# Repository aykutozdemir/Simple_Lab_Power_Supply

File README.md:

### Simple Lab Power Supply (4-Channel)

A compact four-channel bench power supply project with dedicated controller, protection, and current-sensing boards, plus a printable enclosure and front panel components. Repository: [`aykutozdemir/Simple_Lab_Power_Supply`](https://github.com/aykutozdemir/Simple_Lab_Power_Supply).

### Features
- **Four independent channels**: adjustable and monitorable per-channel output
- **Dedicated protection**: over-current/short-circuit protection board
- **Current sensing**: separate current sensor design for precise measurement
- **Printable enclosure**: parametric SCAD and exported STLs for all case parts
- **Fabrication-ready**: gerbers, BOMs, PDFs, and 3D previews included

### Repository layout
- `Controller/`: KiCad project for the main control PCB
  - `generated/gerbers/`: fabrication files
  - `generated/bom/`: BOM in CSV/HTML/PDF
  - `generated/pdf/`: PCB and schematic PDFs
  - `generated/3d/`: 3D renders and board STEP/STL
- `Protection/`: KiCad project for the protection PCB
  - `generated/` mirrors the structure above
- `Current_Sensor/`: KiCad project for the current sensor
- `3D/`: mechanical assets and enclosure
  - `exports/`: printable panels and enclosure parts (`front.stl`, `back.stl`, `left.stl`, `right.stl`, `top.stl`, `bottom.stl`, `mid.stl`)
  - subfolders for off-the-shelf or custom components (banana jacks, fan, sockets, switches, knobs, etc.)

### Quick start
1) Open electronics in KiCad (KiCad 7+ recommended):
   - `Controller/Controller.kicad_pro`
   - `Protection/Protection.kicad_pro`
   - `Current_Sensor/Current_Sensor.kicad_pro`
2) Fabrication files:
   - Controller gerbers: `Controller/generated/gerbers/`
   - Protection gerbers: `Protection/generated/gerbers/`
   - BOMs: `Controller/generated/bom/Controller_bom.*`, `Protection/generated/bom/Protection_bom.*`
   - PDFs (schematic/PCB): see `generated/pdf/`
3) Enclosure and front panel:
   - Print from `3D/exports/*.stl`
   - Optional components located in subfolders (e.g., `3D/banana/banana.stl`, `3D/pot/pot.stl`, `3D/fan/fan.stl`)

### 3D printing guidance
- Material: PLA or PETG (PETG recommended for heat resistance)
- Layer height: 0.2 mm (typ.)
- Infill: 15–25% grid/gyroid for panels; 35–50% for brackets
- Walls: 3–4 perimeters; 4–6 top/bottom layers
- Orientation: print panels flat; brackets with load-bearing axis aligned; check STL previews in `3D/exports/`

### Front panel notes
- Displays and meters mount to the `front.stl` panel. Matching cutouts are modeled in the exported panel.
- Banana connectors: use `3D/banana/banana.stl`. In the assembled view, place two banana connectors per multimeter, horizontally below the displays, visible from front. Front panel hole x-offsets at ±12 mm and z at `box_height*4/6 - multimeter_height/2 - 25`. Place connectors at y slightly in front of the front panel (e.g., `box_depth + 1`) and rotate `[-90, 0, 0]` for insertion alignment [[memory:6634135]].

### Electrical overview
- Controller board manages channel outputs, measurement, and user interface.
- Protection board implements fast over-current/short protection and isolation where needed.
- Current sensor board provides per-channel current measurement with appropriate scaling.
- See the comprehensive PDFs in `Controller/generated/pdf/` and `Protection/generated/pdf/` for signal names and interfaces.

### Fabrication and assembly
1) Order PCBs using the gerbers in each project’s `generated/gerbers/` directory.
2) Source parts from the BOMs (`generated/bom/`). Check packages/footprints against PDFs.
3) Solder SMD/TH components as per schematics.
4) Test each board independently before system integration.
5) Assemble enclosure:
   - Dry-fit `front`, `back`, `left`, `right`, `top`, `bottom`, and `mid` panels.
   - Install switches, sockets, fuses, fan, pots/knobs, and banana jacks.
   - Route wiring according to schematics; keep high-current and low-noise paths separated.

### Safety
- Mains voltages and high currents can be hazardous. Verify isolation, fusing, and protective earth where applicable.
- Use appropriate gauge wiring, strain relief, and insulation. Validate thermal performance under load.

### Contributing
- Issues and pull requests are welcome on GitHub: `https://github.com/aykutozdemir/Simple_Lab_Power_Supply`.
- For changes that affect the enclosure, export updated STLs to `3D/exports/` and include screenshots/renders.
- For PCB edits, regenerate `generated/` assets (BOM, PDFs, gerbers) so reviewers can diff artifacts.

### License
No license file is included yet. If you intend to reuse or distribute, please open an issue to clarify licensing, or add a `LICENSE` file.

### Credits
Design and repository maintained by Aykut Ozdemir. See the GitHub repository for history and updates: [`Simple_Lab_Power_Supply`](https://github.com/aykutozdemir/Simple_Lab_Power_Supply).

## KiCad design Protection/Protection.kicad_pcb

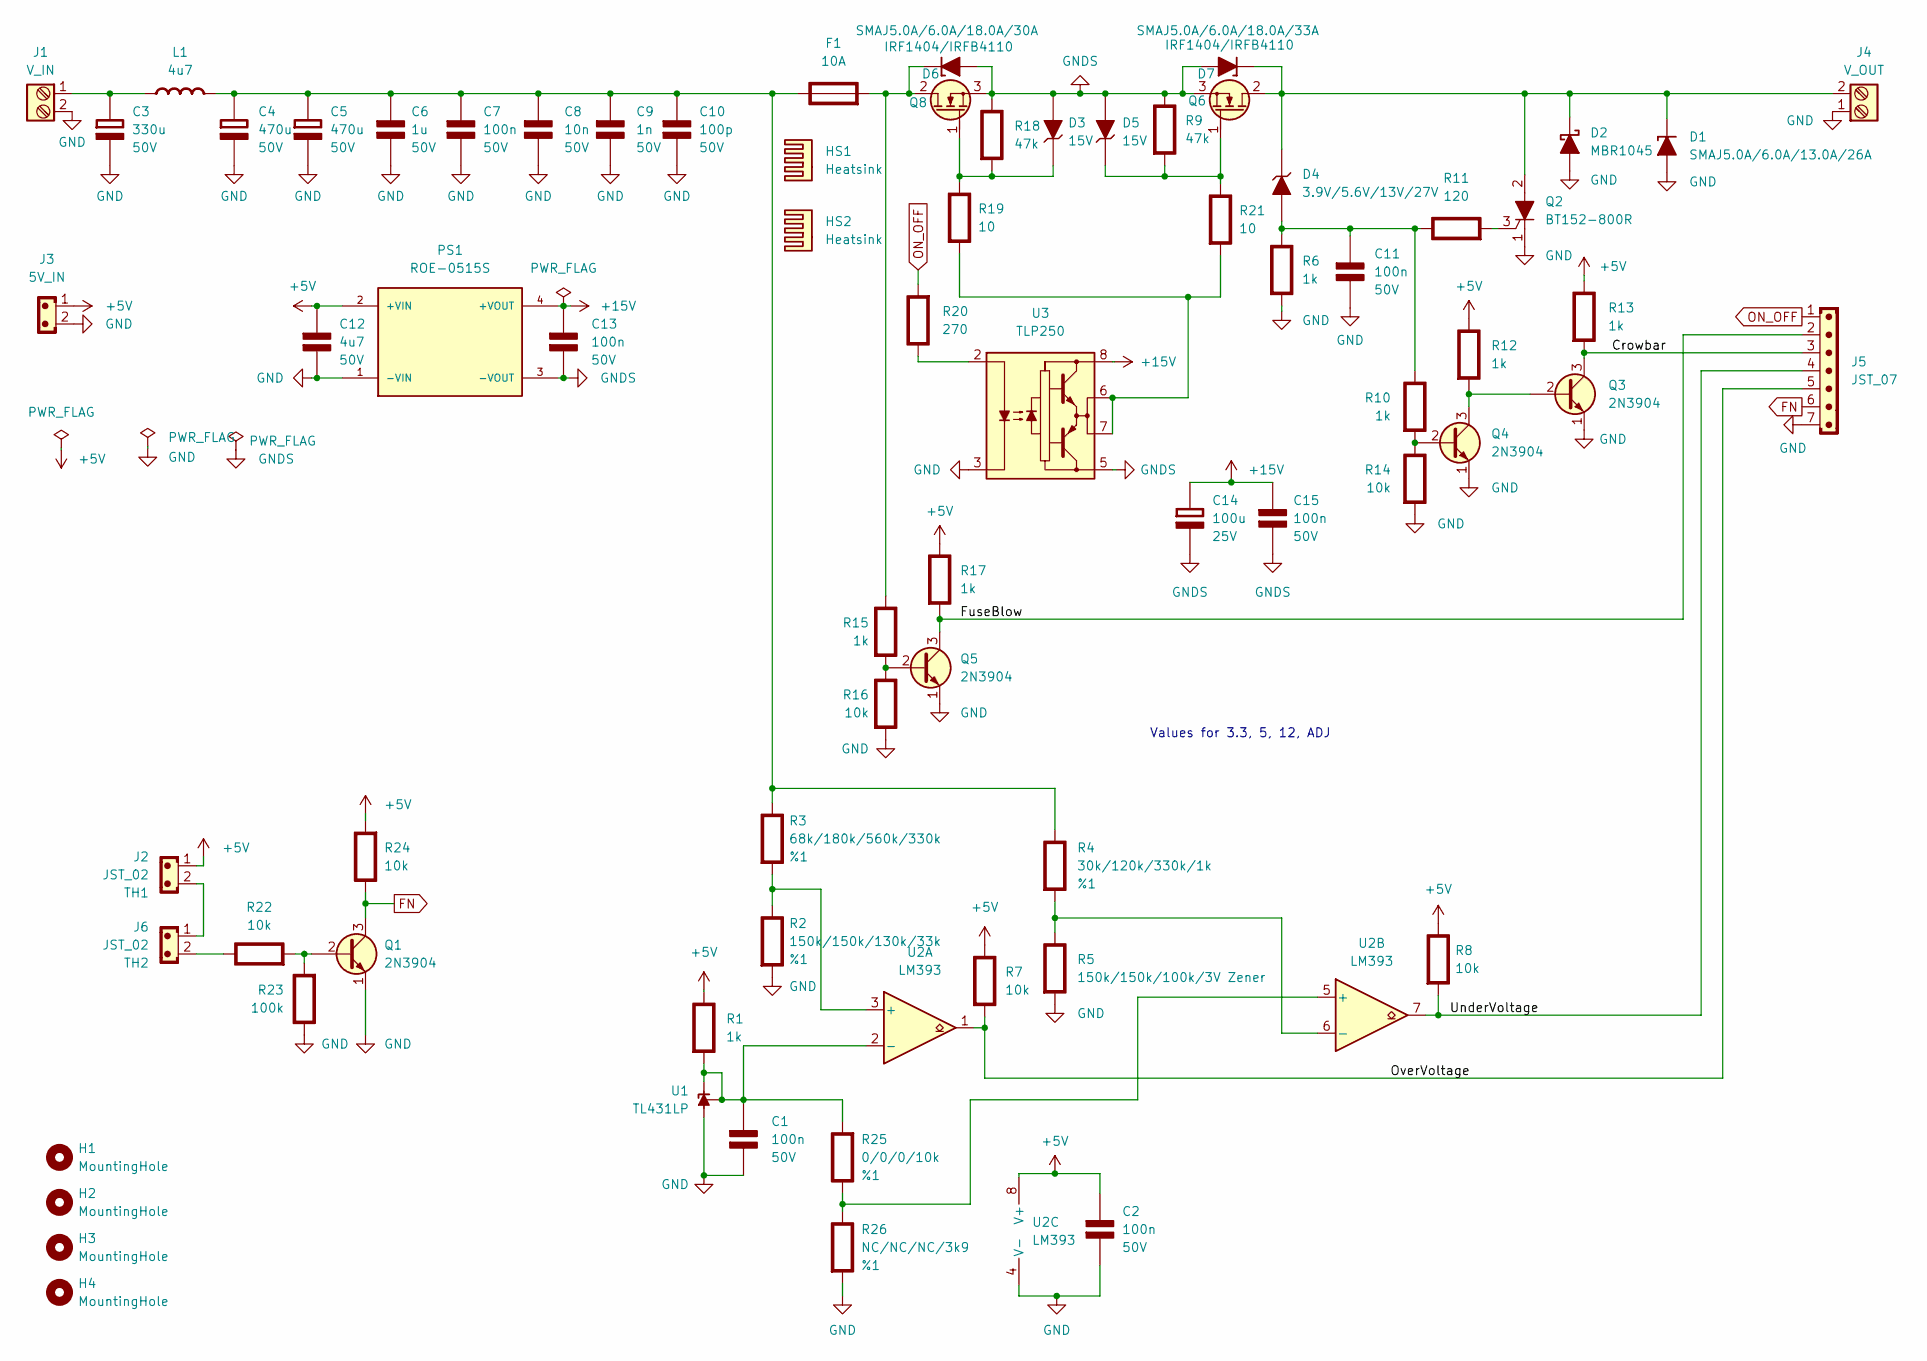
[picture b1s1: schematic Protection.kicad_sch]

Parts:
C1, C2, C7, C11, C13, C15: 100n; C_Disc_D5.0mm_W2.5mm_P5.00mm; Rating 50V
C3: 330u; CP_Radial_D10.0mm_P5.00mm; Rating 50V
C4, C5: 470u; C_Radial_D10.0mm_H20.0mm_P5.00mm; Rating 50V
C6: 1u; C_Disc_D5.0mm_W2.5mm_P5.00mm; Rating 50V
C8: 10n; C_Disc_D5.0mm_W2.5mm_P5.00mm; Rating 50V
C9: 1n; C_Disc_D5.0mm_W2.5mm_P5.00mm; Rating 50V
C10: 100p; C_Disc_D5.0mm_W2.5mm_P5.00mm; Rating 50V
C12: 4u7; C_1206_3216Metric_Pad1.33x1.80mm_HandSolder; Rating 50V
C14: 100u; CP_Radial_D5.0mm_P2.50mm; Rating 25V
D1: SMAJ5.0A/6.0A/13.0A/26A; D_SMA
D2: MBR1045; TO-220-2_Vertical_KA
D3, D5: 15V; D_DO-41_SOD81_P10.16mm_Horizontal
D4: 3.9V/5.6V/13V/27V; D_DO-41_SOD81_P10.16mm_Horizontal
D6: SMAJ5.0A/6.0A/18.0A/30A; D_SMA
D7: SMAJ5.0A/6.0A/18.0A/33A; D_SMA
F1: 10A; TerminalBlock_Phoenix_PT-1,5-2-5.0-H_1x02_P5.00mm_Horizontal
H1, H2, H3, H4: MountingHole; MountingHole_3.2mm_M3_DIN965
HS1, HS2: Heatsink; TO-220_Heatsink
J1: V_IN; TerminalBlock_Phoenix_PT-1,5-2-5.0-H_1x02_P5.00mm_Horizontal
J2, J6: JST_02; JST_EH_B2B-EH-A_1x02_P2.50mm_Vertical
J3: 5V_IN; JST_XH_B2B-XH-A_1x02_P2.50mm_Vertical
J4: V_OUT; TerminalBlock_Phoenix_PT-1,5-2-5.0-H_1x02_P5.00mm_Horizontal
J5: JST_07; JST_XH_B7B-XH-A_1x07_P2.50mm_Vertical
L1: 4u7; L_12x12mm_H8mm; Rating 15A
PS1: ROE-0515S; CONV_ROE-0515S; PARTREV 5
Q1, Q3, Q4, Q5: 2N3904; TO-92_Inline_Wide_EBC
Q2: BT152-800R; TO-220-3_Vertical_KAG
Q6, Q8: IRF1404/IRFB4110; TO-220-3_Vertical_GDS
R1, R6, R10, R12, R13, R15, R17: 1k; R_Axial_DIN0207_L6.3mm_D2.5mm_P10.16mm_Horizontal
R2: 150k/150k/130k/33k; R_Axial_DIN0207_L6.3mm_D2.5mm_P10.16mm_Horizontal; Rating %1
R3: 68k/180k/560k/330k; R_Axial_DIN0207_L6.3mm_D2.5mm_P10.16mm_Horizontal; Rating %1
R4: 30k/120k/330k/1k; R_Axial_DIN0207_L6.3mm_D2.5mm_P10.16mm_Horizontal; Rating %1
R5: 150k/150k/100k/3V Zener; R_Axial_DIN0207_L6.3mm_D2.5mm_P10.16mm_Horizontal; Rating %1
R7, R8: 10k; R_Axial_DIN0207_L6.3mm_D2.5mm_P10.16mm_Horizontal; Rating %1
R9, R18: 47k; R_Axial_DIN0207_L6.3mm_D2.5mm_P10.16mm_Horizontal
R11: 120; R_Axial_DIN0207_L6.3mm_D2.5mm_P10.16mm_Horizontal
R14, R16, R22, R24: 10k; R_Axial_DIN0207_L6.3mm_D2.5mm_P10.16mm_Horizontal
R19, R21: 10; R_Axial_DIN0207_L6.3mm_D2.5mm_P10.16mm_Horizontal
R20: 270; R_Axial_DIN0207_L6.3mm_D2.5mm_P10.16mm_Horizontal
R23: 100k; R_Axial_DIN0207_L6.3mm_D2.5mm_P10.16mm_Horizontal
R25: 0/0/0/10k; R_Axial_DIN0207_L6.3mm_D2.5mm_P10.16mm_Horizontal; Rating %1
R26: NC/NC/NC/3k9; R_Axial_DIN0207_L6.3mm_D2.5mm_P10.16mm_Horizontal; Rating %1
U1: TL431LP; TO-92_Inline
U2: LM393; DIP-8_W7.62mm_Socket
U3: TLP250; DIP-8_W7.62mm

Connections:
+5V: C2.1 (+), C12.1 (+), J2.1, J3.1, PS1.2 (+VIN), R1.1 (+), R7.1 (+), R8.1 (+), R12.1 (+), R13.1 (+), R17.1 (+), R24.2 (-), U2.8 (V+)
+15V: C13.1 (+), C14.1 (+), C15.1 (+), PS1.4 (+VOUT), U3.8 (VCC)
/Crowbar: J5.3, Q3.3 (C), R13.2 (-)
/FuseBlow: J5.2, Q5.3 (C), R17.2 (-)
/OverVoltage: J5.5, R7.2 (-), U2.1
/UnderVoltage: J5.4, R8.2 (-), U2.7
FN: J5.6, Q1.3 (C), R24.1 (+)
GND: C1.2 (-), C2.2 (-), C3.2 (-), C4.2 (-), C5.2 (-), C6.2 (-), C7.2 (-), C8.2 (-), C9.2 (-), C10.2 (-), C11.2 (-), C12.2 (-), D1.2 (A), D2.2 (A), J1.2, J3.2, J4.1, J5.7, PS1.1 (-VIN), Q1.1 (E), Q2.1 (K), Q3.1 (E), Q4.1 (E), Q5.1 (E), R2.2 (-), R5.2 (-), R6.2 (-), R14.2 (-), R16.2 (-), R23.1 (+), R26.2 (-), U1.2 (A), U2.4 (V-), U3.3 (C)
GNDS: C13.2 (-), C14.2 (-), C15.2 (-), D3.1 (A), D5.1 (A), D6.2 (A), D7.2 (A), PS1.3 (-VOUT), Q6.3 (S), Q8.3 (S), R9.1 (+), R18.1 (+), U3.5 (VEE)
unnamed: C1.1 (+), R1.2 (-), R25.2 (-), U1.1 (REF), U1.3 (K), U2.2 (-)
unnamed: C3.1 (+), J1.1, L1.1 (+)
unnamed: C4.1 (+), C5.1 (+), C6.1 (+), C7.1 (+), C8.1 (+), C9.1 (+), C10.1 (+), F1.1 (+), L1.2 (-), R3.1 (+), R4.1 (+)
unnamed: C11.1 (+), D4.1 (A), R6.1 (+), R10.1 (+), R11.1 (+)
unnamed: D1.1 (K), D2.1 (K), D4.2 (K), D7.1 (K), J4.2, Q2.2 (A), Q6.2 (D)
unnamed: D3.2 (K), Q8.1 (G), R18.2 (-), R19.1 (+)
unnamed: D5.2 (K), Q6.1 (G), R9.2 (-), R21.1 (+)
unnamed: D6.1 (K), F1.2 (-), Q8.2 (D), R15.1 (+)
unnamed: J2.2, J6.1
unnamed: Q1.2 (B), R22.2 (-), R23.2 (-)
unnamed: Q2.3 (G), R11.2 (-)
unnamed: Q3.2 (B), Q4.3 (C), R12.2 (-)
unnamed: Q4.2 (B), R10.2 (-), R14.1 (+)
unnamed: Q5.2 (B), R15.2 (-), R16.1 (+)
unnamed: R2.1 (+), R3.2 (-), U2.3 (+)
unnamed: R4.2 (-), R5.1 (+), U2.6 (-)
unnamed: R19.2 (-), R21.2 (-), U3.6 (VO), U3.7 (VO)
unnamed: R20.1 (+), U3.2 (A)
unnamed: J6.2, R22.1 (+)
unnamed: R25.1 (+), R26.1 (+), U2.5 (+)
ON_OFF: J5.1, R20.2 (-)

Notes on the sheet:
Values for 3.3, 5, 12, ADJ

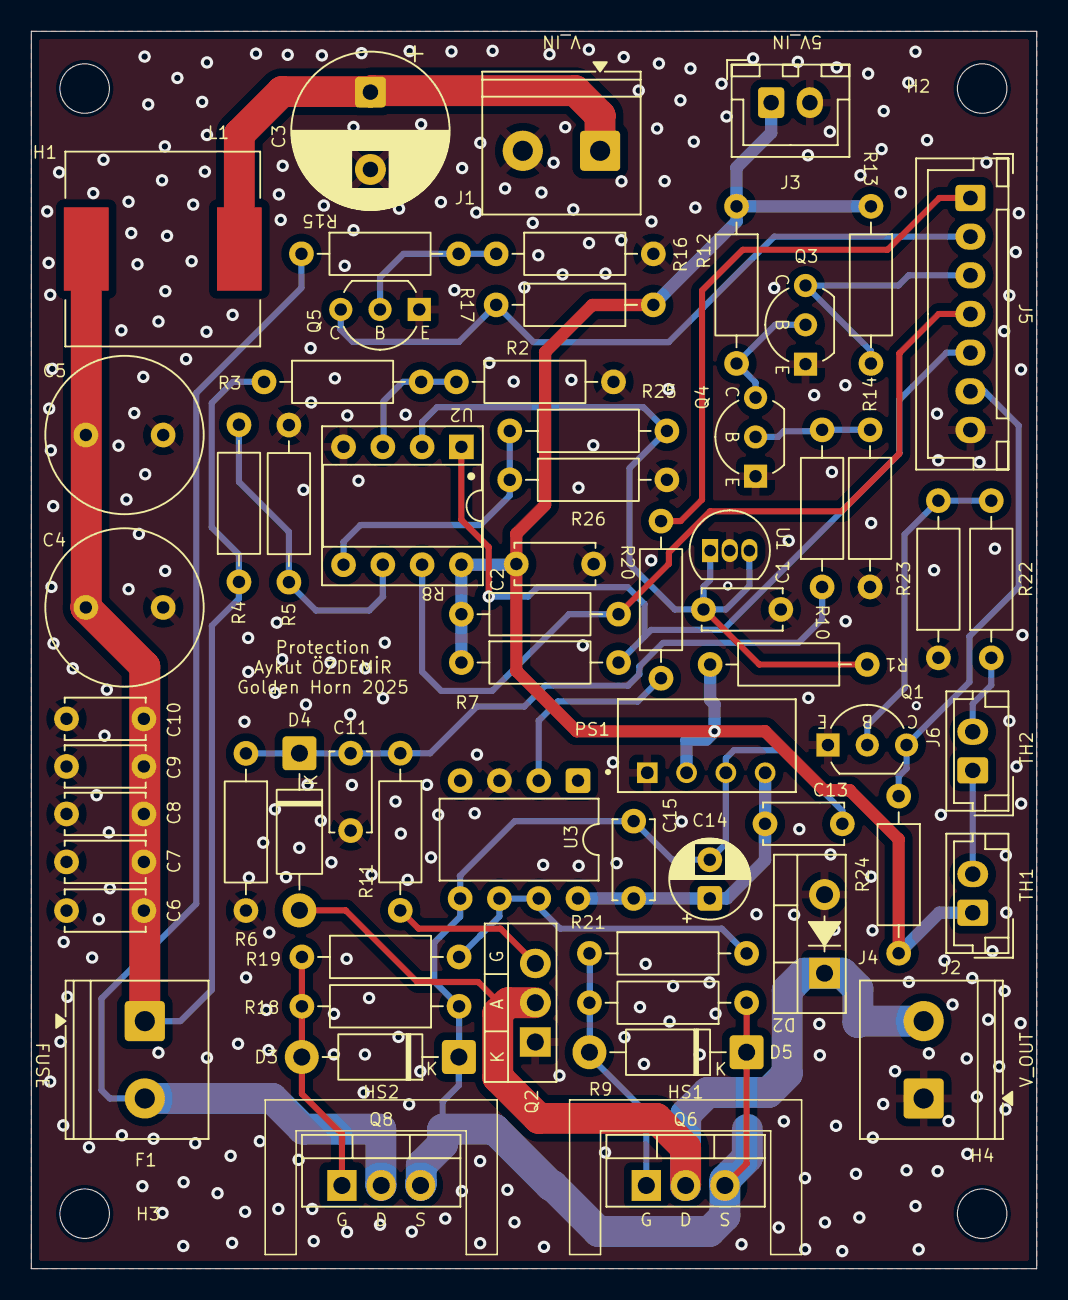
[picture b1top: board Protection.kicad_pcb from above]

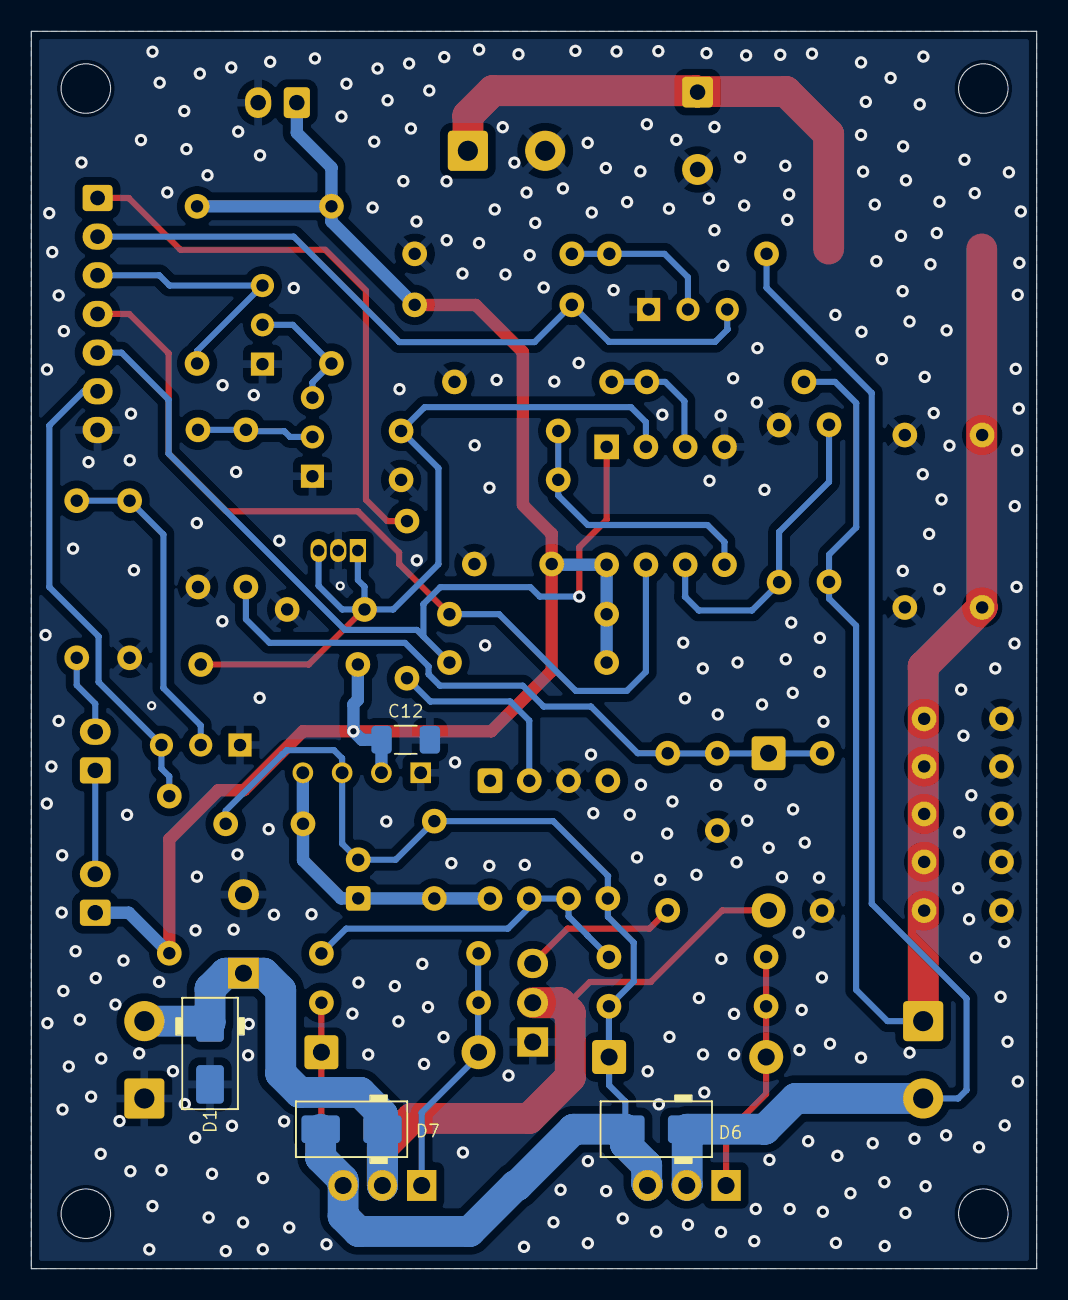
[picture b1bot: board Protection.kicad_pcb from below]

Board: 2 copper layers, 65.0 x 80.0 mm, 73 parts (4 on the bottom side), 30 nets.

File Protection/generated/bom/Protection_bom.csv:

"Refs","Value","Footprint","Qty","Rating"
"C10","100p","Capacitor_THT:C_Disc_D5.0mm_W2.5mm_P5.00mm","1","50V"
"C9","1n","Capacitor_THT:C_Disc_D5.0mm_W2.5mm_P5.00mm","1","50V"
"C8","10n","Capacitor_THT:C_Disc_D5.0mm_W2.5mm_P5.00mm","1","50V"
"C1,C2,C7,C11,C13,C15","100n","Capacitor_THT:C_Disc_D5.0mm_W2.5mm_P5.00mm","6","50V"
"C6","1u","Capacitor_THT:C_Disc_D5.0mm_W2.5mm_P5.00mm","1","50V"
"C14","100u","Capacitor_THT:CP_Radial_D5.0mm_P2.50mm","1","25V"
"C3","330u","Capacitor_THT:CP_Radial_D10.0mm_P5.00mm","1","50V"
"C4,C5","470u","Capacitor_THT:C_Radial_D10.0mm_H20.0mm_P5.00mm","2","50V"
"J3","5V_IN","Connector_JST:JST_XH_B2B-XH-A_1x02_P2.50mm_Vertical","1",""
"F1","10A","TerminalBlock_Phoenix:TerminalBlock_Phoenix_PT-1,5-2-5.0-H_1x02_P5.00mm_Horizontal","1",""
"R19,R21","10","Resistor_THT:R_Axial_DIN0207_L6.3mm_D2.5mm_P10.16mm_Horizontal","2",""
"D3,D5","15V","Diode_THT:D_DO-41_SOD81_P10.16mm_Horizontal","2",""
"R11","120","Resistor_THT:R_Axial_DIN0207_L6.3mm_D2.5mm_P10.16mm_Horizontal","1",""
"R20","270","Resistor_THT:R_Axial_DIN0207_L6.3mm_D2.5mm_P10.16mm_Horizontal","1",""
"R1,R6,R10,R12,R13,R15,R17","1k","Resistor_THT:R_Axial_DIN0207_L6.3mm_D2.5mm_P10.16mm_Horizontal","7",""
"R7,R8","10k","Resistor_THT:R_Axial_DIN0207_L6.3mm_D2.5mm_P10.16mm_Horizontal","2","%1"
"R14,R16,R22,R24","10k","Resistor_THT:R_Axial_DIN0207_L6.3mm_D2.5mm_P10.16mm_Horizontal","4",""
"R9,R18","47k","Resistor_THT:R_Axial_DIN0207_L6.3mm_D2.5mm_P10.16mm_Horizontal","2",""
"R23","100k","Resistor_THT:R_Axial_DIN0207_L6.3mm_D2.5mm_P10.16mm_Horizontal","1",""
"R25","0/0/0/10k","Resistor_THT:R_Axial_DIN0207_L6.3mm_D2.5mm_P10.16mm_Horizontal","1","%1"
"R5","150k/150k/100k/3V Zener","Resistor_THT:R_Axial_DIN0207_L6.3mm_D2.5mm_P10.16mm_Horizontal","1","%1"
"R2","150k/150k/130k/33k","Resistor_THT:R_Axial_DIN0207_L6.3mm_D2.5mm_P10.16mm_Horizontal","1","%1"
"Q1,Q3-Q5","2N3904","PCM_Package_TO_SOT_THT_AKL:TO-92_Inline_Wide_EBC","4",""
"D4","3.9V/5.6V/13V/27V","Diode_THT:D_DO-41_SOD81_P10.16mm_Horizontal","1",""
"R4","30k/120k/330k/1k","Resistor_THT:R_Axial_DIN0207_L6.3mm_D2.5mm_P10.16mm_Horizontal","1","%1"
"C12","4u7","Capacitor_SMD:C_1206_3216Metric_Pad1.33x1.80mm_HandSolder","1","50V"
"L1","4u7","Inductor_SMD:L_12x12mm_H8mm","1","15A"
"R3","68k/180k/560k/330k","Resistor_THT:R_Axial_DIN0207_L6.3mm_D2.5mm_P10.16mm_Horizontal","1","%1"
"Q2","BT152-800R","PCM_Package_TO_SOT_THT_AKL:TO-220-3_Vertical_KAG","1",""
"HS1,HS2","Heatsink","Power_Module_Library:TO-220_Heatsink","2",""
"Q6,Q8","IRF1404/IRFB4110","PCM_Package_TO_SOT_THT_AKL:TO-220-3_Vertical_GDS","2",""
"J2,J6","JST_02","Connector_JST:JST_EH_B2B-EH-A_1x02_P2.50mm_Vertical","2",""
"J5","JST_07","Connector_JST:JST_XH_B7B-XH-A_1x07_P2.50mm_Vertical","1",""
"U2","LM393","PCM_Package_DIP_AKL:DIP-8_W7.62mm_Socket","1",""
"D2","MBR1045","PCM_Package_TO_SOT_THT_AKL:TO-220-2_Vertical_KA","1",""
"R26","NC/NC/NC/3k9","Resistor_THT:R_Axial_DIN0207_L6.3mm_D2.5mm_P10.16mm_Horizontal","1","%1"
"PS1","ROE-0515S","Isolation_Trafo:CONV_ROE-0515S","1",""
"D1","SMAJ5.0A/6.0A/13.0A/26A","PCM_Diode_SMD_AKL:D_SMA","1",""
"D6","SMAJ5.0A/6.0A/18.0A/30A","PCM_Diode_SMD_AKL:D_SMA","1",""
"D7","SMAJ5.0A/6.0A/18.0A/33A","PCM_Diode_SMD_AKL:D_SMA","1",""
"U1","TL431LP","Package_TO_SOT_THT:TO-92_Inline","1",""
"U3","TLP250","Package_DIP:DIP-8_W7.62mm","1",""
"J1","V_IN","TerminalBlock_Phoenix:TerminalBlock_Phoenix_PT-1,5-2-5.0-H_1x02_P5.00mm_Horizontal","1",""
"J4","V_OUT","TerminalBlock_Phoenix:TerminalBlock_Phoenix_PT-1,5-2-5.0-H_1x02_P5.00mm_Horizontal","1",""

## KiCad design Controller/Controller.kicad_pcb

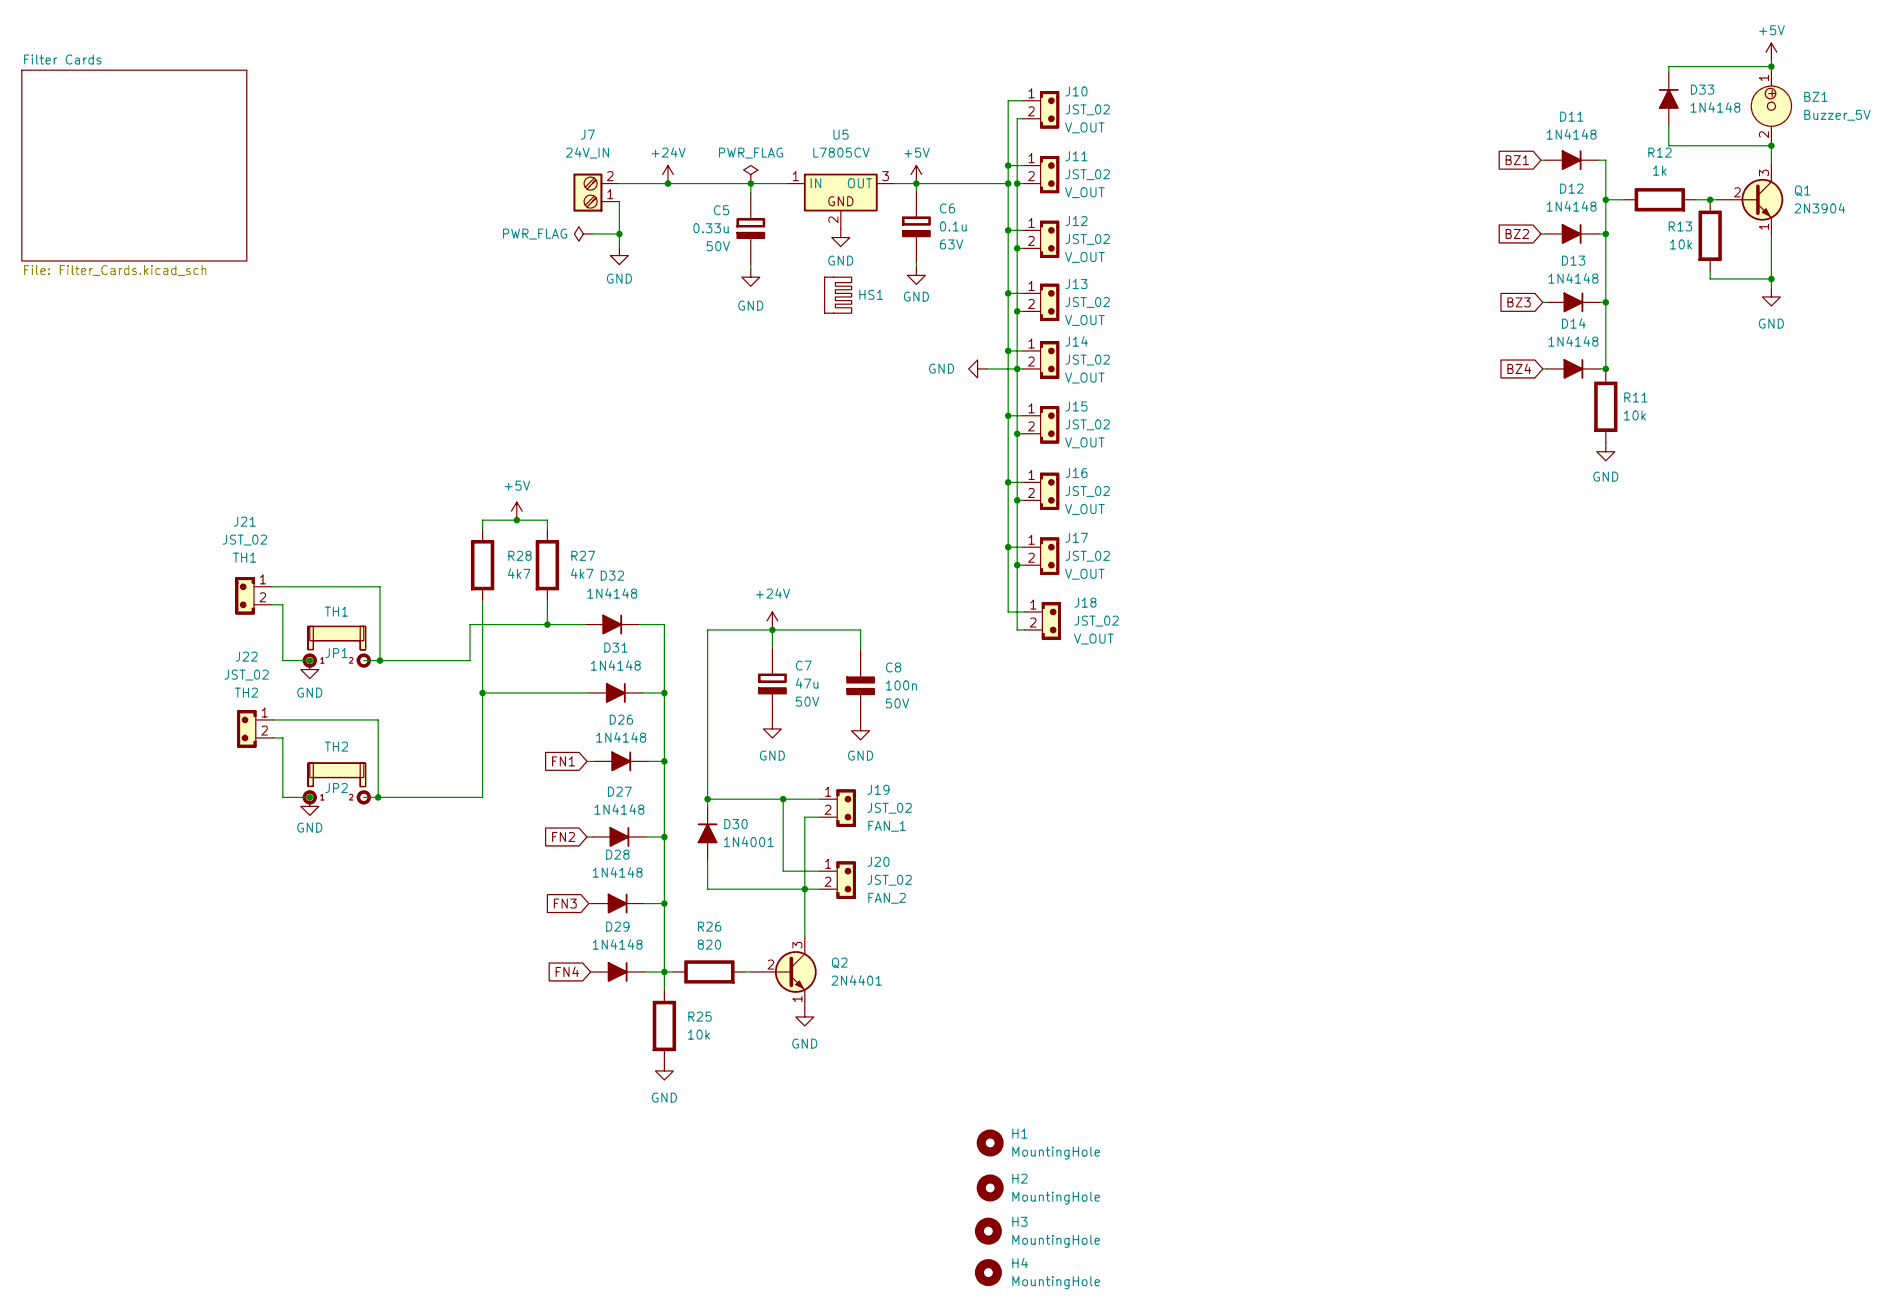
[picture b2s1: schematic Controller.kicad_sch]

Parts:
BZ1: Buzzer_5V; Buzzer_12x9.5RM7.6
C5: 0.33u; CP_Radial_Tantal_D5.5mm_P5.00mm; Rating 50V
C6: 0.1u; CP_Radial_Tantal_D5.5mm_P5.00mm; Rating 63V
C7: 47u; C_Radial_D6.3mm_H11.0mm_P2.50mm; Rating 50V
C8: 100n; C_Disc_D5.0mm_W2.5mm_P5.00mm; Rating 50V
D11, D12, D13, D14, D26, D27, D28, D29, D31, D32, D33: 1N4148; D_DO-35_SOD27_P7.62mm_Horizontal
D30: 1N4001; D_DO-41_SOD81_P7.62mm_Horizontal
H1, H2, H3, H4: MountingHole; MountingHole_3.2mm_M3_DIN965
HS1: Heatsink_Generic; TO-220_Heatsink
J7: Screw_Terminal_2_P5.00mm; TerminalBlock_Phoenix_PT-1,5-2-5.0-H_1x02_P5.00mm_Horizontal
J10, J11, J12, J13, J14, J15, J16, J17, J18, J19, J20, J21, J22: JST_02; JST_XH_B2B-XH-A_1x02_P2.50mm_Vertical
JP1, JP2: PinHeader_1x02_P2.54mm_Vertical
Q1: 2N3904; TO-92_Inline_Wide_EBC
Q2: 2N4401; TO-92_Inline_Wide_EBC
R11, R13, R25: 10k; R_Axial_DIN0207_L6.3mm_D2.5mm_P10.16mm_Horizontal
R12: 1k; R_Axial_DIN0207_L6.3mm_D2.5mm_P10.16mm_Horizontal
R26: 820; R_Axial_DIN0207_L6.3mm_D2.5mm_P10.16mm_Horizontal
R27, R28: 4k7; R_Axial_DIN0207_L6.3mm_D2.5mm_P10.16mm_Horizontal
U5: L7805CV; TO-220-3_Vertical

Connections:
+5V: BZ1.1, C6.1 (+), D33.1 (K), J10.1, J11.1, J12.1, J13.1, J14.1, J15.1, J16.1, J17.1, J18.1, R27.1 (+), R28.1 (+), U5.3 (OUT); also elsewhere on the board
+24V: C5.1 (+), C7.1 (+), C8.1 (+), D30.1 (K), J7.2, J19.1, J20.1, U5.1 (IN)
BZ1: D11.2 (A); also elsewhere on the board
BZ2: D12.2 (A); also elsewhere on the board
BZ3: D13.2 (A); also elsewhere on the board
BZ4: D14.2 (A); also elsewhere on the board
FN1: D26.2 (A); also elsewhere on the board
FN2: D27.2 (A); also elsewhere on the board
FN3: D28.2 (A); also elsewhere on the board
FN4: D29.2 (A); also elsewhere on the board
GND: C5.2 (-), C6.2 (-), C7.2 (-), C8.2 (-), J7.1, J10.2, J11.2, J12.2, J13.2, J14.2, J15.2, J16.2, J17.2, J18.2, J21.2, J22.2, JP1.1, JP2.1, Q1.1 (E), Q2.1 (E), R11.2 (-), R13.2 (-), R25.2 (-), U5.2; also elsewhere on the board
unnamed: D11.1 (K), D12.1 (K), D13.1 (K), D14.1 (K), R11.1 (+), R12.1 (+)
unnamed: D26.1 (K), D27.1 (K), D28.1 (K), D29.1 (K), D31.1 (K), D32.1 (K), R25.1 (+), R26.1 (+)
unnamed: D30.2 (A), J19.2, J20.2, Q2.3 (C)
unnamed: D31.2 (A), J22.1, JP2.2, R28.2 (-)
unnamed: D32.2 (A), J21.1, JP1.2, R27.2 (-)
unnamed: BZ1.2, D33.2 (A), Q1.3 (C)
unnamed: Q1.2 (B), R12.2 (-), R13.1 (+)
unnamed: Q2.2 (B), R26.2 (-)

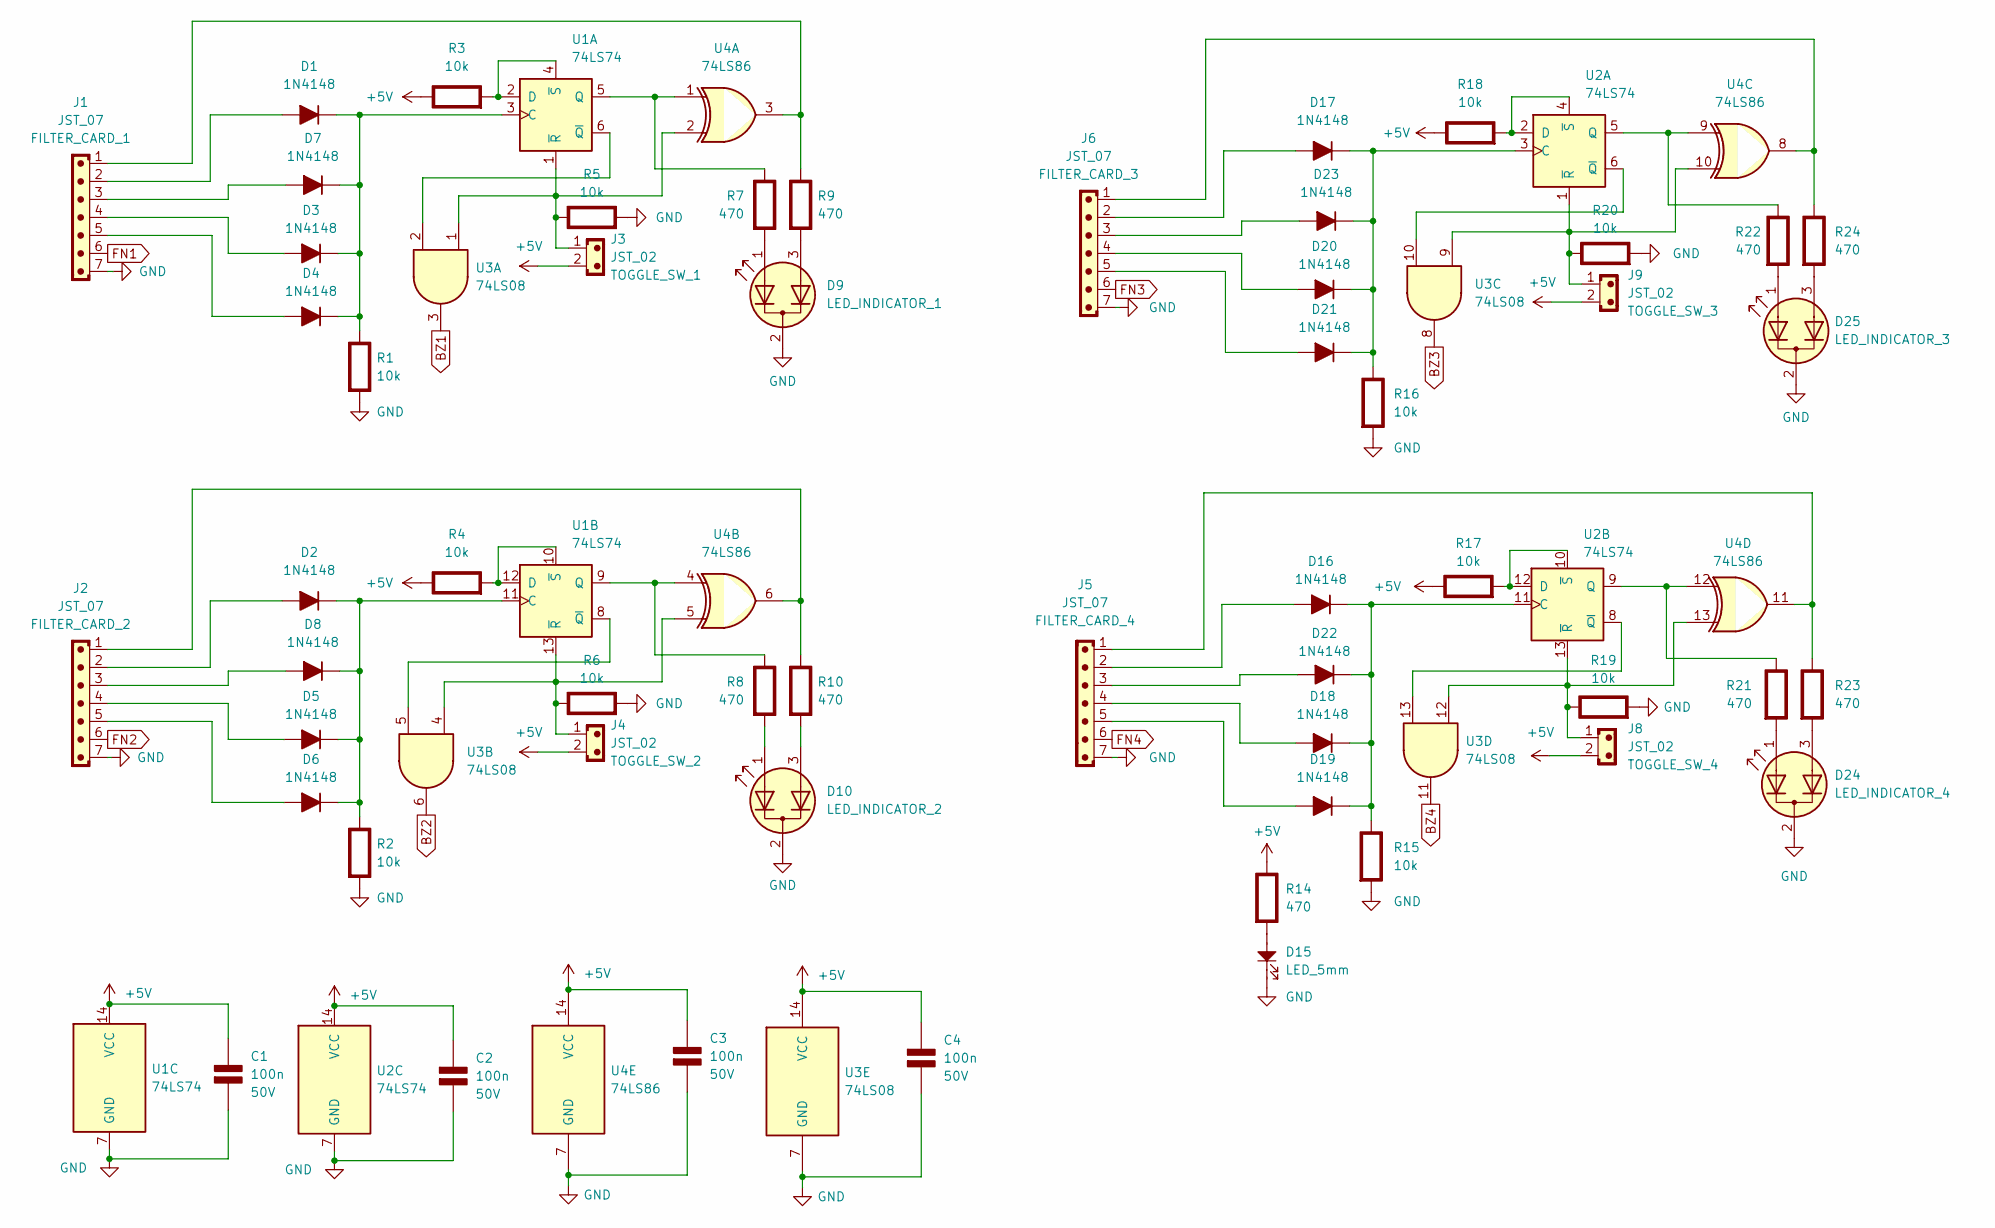
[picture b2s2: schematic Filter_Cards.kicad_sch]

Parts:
C1, C2, C3, C4: 100n; C_Disc_D5.0mm_W2.5mm_P5.00mm; Rating 50V
D1, D2, D3, D4, D5, D6, D7, D8, D16, D17, D18, D19, D20, D21, D22, D23: 1N4148; D_DO-35_SOD27_P7.62mm_Horizontal
D9, D10, D24, D25: LED_Dual_AKA; JST_XH_B3B-XH-A_1x03_P2.50mm_Vertical
D15: LED_5mm; JST_XH_B2B-XH-A_1x02_P2.50mm_Vertical
J1, J2, J5, J6: JST_07; JST_XH_B7B-XH-A_1x07_P2.50mm_Vertical
J3, J4, J8, J9: JST_02; JST_XH_B2B-XH-A_1x02_P2.50mm_Vertical
R1, R2, R15, R16: 10k; R_Axial_DIN0207_L6.3mm_D2.5mm_P10.16mm_Horizontal
R3, R4, R5, R6, R17, R18, R19, R20: 10k; R_Axial_DIN0207_L6.3mm_D2.5mm_P10.16mm_Horizontal; Rating %1
R7, R8, R9, R10, R14, R21, R22, R23, R24: 470; R_Axial_DIN0207_L6.3mm_D2.5mm_P10.16mm_Horizontal; Rating %1
U1, U2: 74LS74; DIP-14_W7.62mm_Socket
U3: 74LS08; DIP-14_W7.62mm_Socket
U4: 74LS86; DIP-14_W7.62mm_Socket

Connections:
+5V: C1.1 (+), C2.1 (+), C3.1 (+), C4.1 (+), J3.2, J4.2, J8.2, J9.2, R3.1 (+), R4.1 (+), R14.1 (+), R17.1 (+), R18.1 (+), U1.14 (VCC), U2.14 (VCC), U3.14 (VCC), U4.14 (VCC); also elsewhere on the board
BZ1: U3.3; also elsewhere on the board
BZ2: U3.6; also elsewhere on the board
BZ3: U3.8; also elsewhere on the board
BZ4: U3.11; also elsewhere on the board
FN1: J1.6; also elsewhere on the board
FN2: J2.6; also elsewhere on the board
FN3: J6.6; also elsewhere on the board
FN4: J5.6; also elsewhere on the board
GND: C1.2 (-), C2.2 (-), C3.2 (-), C4.2 (-), D9.2 (K), D10.2 (K), D15.1, D24.2 (K), D25.2 (K), J1.7, J2.7, J5.7, J6.7, R1.2 (-), R2.2 (-), R5.2 (-), R6.2 (-), R15.2 (-), R16.2 (-), R19.2 (-), R20.2 (-), U1.7 (GND), U2.7 (GND), U3.7 (GND), U4.7 (GND); also elsewhere on the board
unnamed: D1.2 (A), J1.2
unnamed: D1.1 (K), D3.1 (K), D4.1 (K), D7.1 (K), R1.1 (+), U1.3 (C)
unnamed: D2.2 (A), J2.2
unnamed: D2.1 (K), D5.1 (K), D6.1 (K), D8.1 (K), R2.1 (+), U1.11 (C)
unnamed: D3.2 (A), J1.4
unnamed: D4.2 (A), J1.5
unnamed: D5.2 (A), J2.4
unnamed: D6.2 (A), J2.5
unnamed: D7.2 (A), J1.3
unnamed: D8.2 (A), J2.3
unnamed: D9.1 (A1), R7.2 (-)
unnamed: D9.3 (A2), R9.2 (-)
unnamed: D10.1 (A1), R8.2 (-)
unnamed: D10.3 (A2), R10.2 (-)
unnamed: D16.2 (A), J5.2
unnamed: D16.1 (K), D18.1 (K), D19.1 (K), D22.1 (K), R15.1 (+), U2.11 (C)
unnamed: D17.2 (A), J6.2
unnamed: D17.1 (K), D20.1 (K), D21.1 (K), D23.1 (K), R16.1 (+), U2.3 (C)
unnamed: D18.2 (A), J5.4
unnamed: D19.2 (A), J5.5
unnamed: D20.2 (A), J6.4
unnamed: D21.2 (A), J6.5
unnamed: D22.2 (A), J5.3
unnamed: D23.2 (A), J6.3
unnamed: D24.1 (A1), R21.2 (-)
unnamed: D24.3 (A2), R23.2 (-)
unnamed: D25.1 (A1), R22.2 (-)
unnamed: D25.3 (A2), R24.2 (-)
unnamed: R3.2 (-), U1.2 (D), U1.4 (~S)
unnamed: R4.2 (-), U1.10 (~S), U1.12 (D)
unnamed: J3.1, R5.1 (+), U1.1 (~R), U3.1, U4.2
unnamed: J4.1, R6.1 (+), U1.13 (~R), U3.4, U4.5
unnamed: R7.1 (+), U1.5 (Q), U4.1
unnamed: R8.1 (+), U1.9 (Q), U4.4
unnamed: J1.1, R9.1 (+), U4.3
unnamed: J2.1, R10.1 (+), U4.6
unnamed: D15.2, R14.2 (-)
unnamed: R17.2 (-), U2.10 (~S), U2.12 (D)
unnamed: R18.2 (-), U2.2 (D), U2.4 (~S)
unnamed: J8.1, R19.1 (+), U2.13 (~R), U3.12, U4.13
unnamed: J9.1, R20.1 (+), U2.1 (~R), U3.9, U4.10
unnamed: R21.1 (+), U2.9 (Q), U4.12
unnamed: R22.1 (+), U2.5 (Q), U4.9
unnamed: J5.1, R23.1 (+), U4.11
unnamed: J6.1, R24.1 (+), U4.8
unnamed: U1.6 (~Q), U3.2
unnamed: U1.8 (~Q), U3.5
unnamed: U2.6 (~Q), U3.10
unnamed: U2.8 (~Q), U3.13

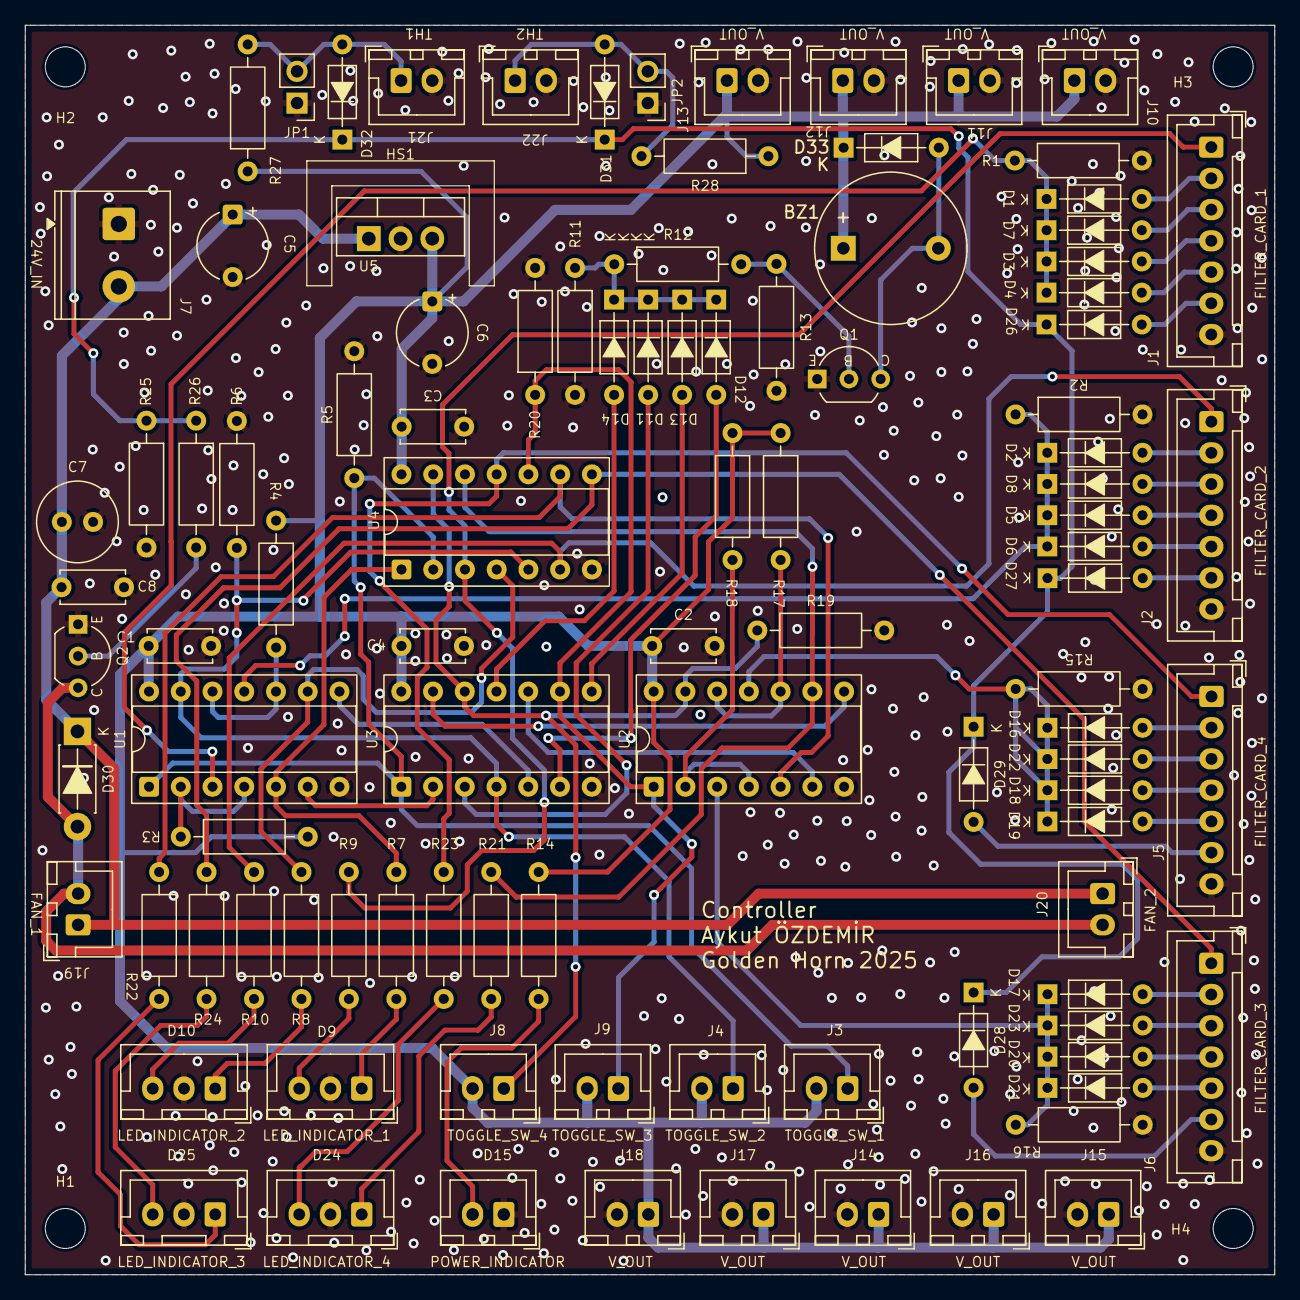
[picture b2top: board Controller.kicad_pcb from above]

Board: 2 copper layers, 100.0 x 100.0 mm, 106 parts (0 on the bottom side), 68 nets.

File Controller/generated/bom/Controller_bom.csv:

"Refs","Value","Footprint","Qty","Rating"
"C6","0.1u","Capacitor_THT:CP_Radial_Tantal_D5.5mm_P5.00mm","1","63V"
"C1-C4,C8","100n","Capacitor_THT:C_Disc_D5.0mm_W2.5mm_P5.00mm","5","50V"
"C5","0.33u","Capacitor_THT:CP_Radial_Tantal_D5.5mm_P5.00mm","1","50V"
"C7","47u","Capacitor_THT:C_Radial_D6.3mm_H11.0mm_P2.50mm","1","50V"
"R7-R10,R14,R21-R24","470","Resistor_THT:R_Axial_DIN0207_L6.3mm_D2.5mm_P10.16mm_Horizontal","9","%1"
"R26","820","Resistor_THT:R_Axial_DIN0207_L6.3mm_D2.5mm_P10.16mm_Horizontal","1",""
"R12","1k","Resistor_THT:R_Axial_DIN0207_L6.3mm_D2.5mm_P10.16mm_Horizontal","1",""
"R1,R2,R11,R13,R15,R16,R25","10k","Resistor_THT:R_Axial_DIN0207_L6.3mm_D2.5mm_P10.16mm_Horizontal","7",""
"R3-R6,R17-R20","10k","Resistor_THT:R_Axial_DIN0207_L6.3mm_D2.5mm_P10.16mm_Horizontal","8","%1"
"D30","1N4001","PCM_Diode_THT_AKL:D_DO-41_SOD81_P7.62mm_Horizontal","1",""
"D1-D8,D11-D14,D16-D23,D26-D29,D31-D33","1N4148","PCM_Diode_THT_AKL:D_DO-35_SOD27_P7.62mm_Horizontal","27",""
"Q1","2N3904","PCM_Package_TO_SOT_THT_AKL:TO-92_Inline_Wide_EBC","1",""
"Q2","2N4401","PCM_Package_TO_SOT_THT_AKL:TO-92_Inline_Wide_EBC","1",""
"R27,R28","4k7","Resistor_THT:R_Axial_DIN0207_L6.3mm_D2.5mm_P10.16mm_Horizontal","2",""
"U3","74LS08","Package_DIP:DIP-14_W7.62mm_Socket","1",""
"U1,U2","74LS74","Package_DIP:DIP-14_W7.62mm_Socket","2",""
"U4","74LS86","Package_DIP:DIP-14_W7.62mm_Socket","1",""
"BZ1","Buzzer_5V","Buzzer_Beeper:Buzzer_12x9.5RM7.6","1",""
"HS1","Heatsink_Generic","Power_Module_Library:TO-220_Heatsink","1",""
"J3,J4,J8-J22","JST_02","Connector_JST:JST_XH_B2B-XH-A_1x02_P2.50mm_Vertical","17",""
"J1,J2,J5,J6","JST_07","Connector_JST:JST_XH_B7B-XH-A_1x07_P2.50mm_Vertical","4",""
"U5","L7805CV","PCM_Package_TO_SOT_THT_AKL:TO-220-3_Vertical","1",""
"D15","LED_5mm","Connector_JST:JST_XH_B2B-XH-A_1x02_P2.50mm_Vertical","1",""
"D9,D10,D24,D25","LED_Dual_AKA","Connector_JST:JST_XH_B3B-XH-A_1x03_P2.50mm_Vertical","4",""
"J7","Screw_Terminal_2_P5.00mm","TerminalBlock_Phoenix:TerminalBlock_Phoenix_PT-1,5-2-5.0-H_1x02_P5.00mm_Horizontal","1",""
"JP1,JP2","~","Connector_PinHeader_2.54mm:PinHeader_1x02_P2.54mm_Vertical","2",""
